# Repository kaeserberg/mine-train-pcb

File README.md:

# Le Train de la Mine - PCB

## Illustrations

<br/>

## Schéma

[Schéma électronique](train-de-mine-schematic.pdf)

## Commande de matériel

- [1 x 8p (1 x 12 pièces)](https://fr.aliexpress.com/item/1005005946834644.html)
- [3 x 2p (3 x 50 pièces)](https://fr.aliexpress.com/item/1005005946834644.html)
- [5x jeu de montage DRG-02](https://fr.aliexpress.com/item/32824633947.html)
- [5x rail DIN 30cm](https://fr.aliexpress.com/item/4001298414947.html)
- [5x ESP32-S3 Mini](https://fr.aliexpress.com/item/1005005449219195.html)
- [1x Connecteur femelle à 2x8 broches (50 pièces)](https://fr.aliexpress.com/item/32604411845.html)

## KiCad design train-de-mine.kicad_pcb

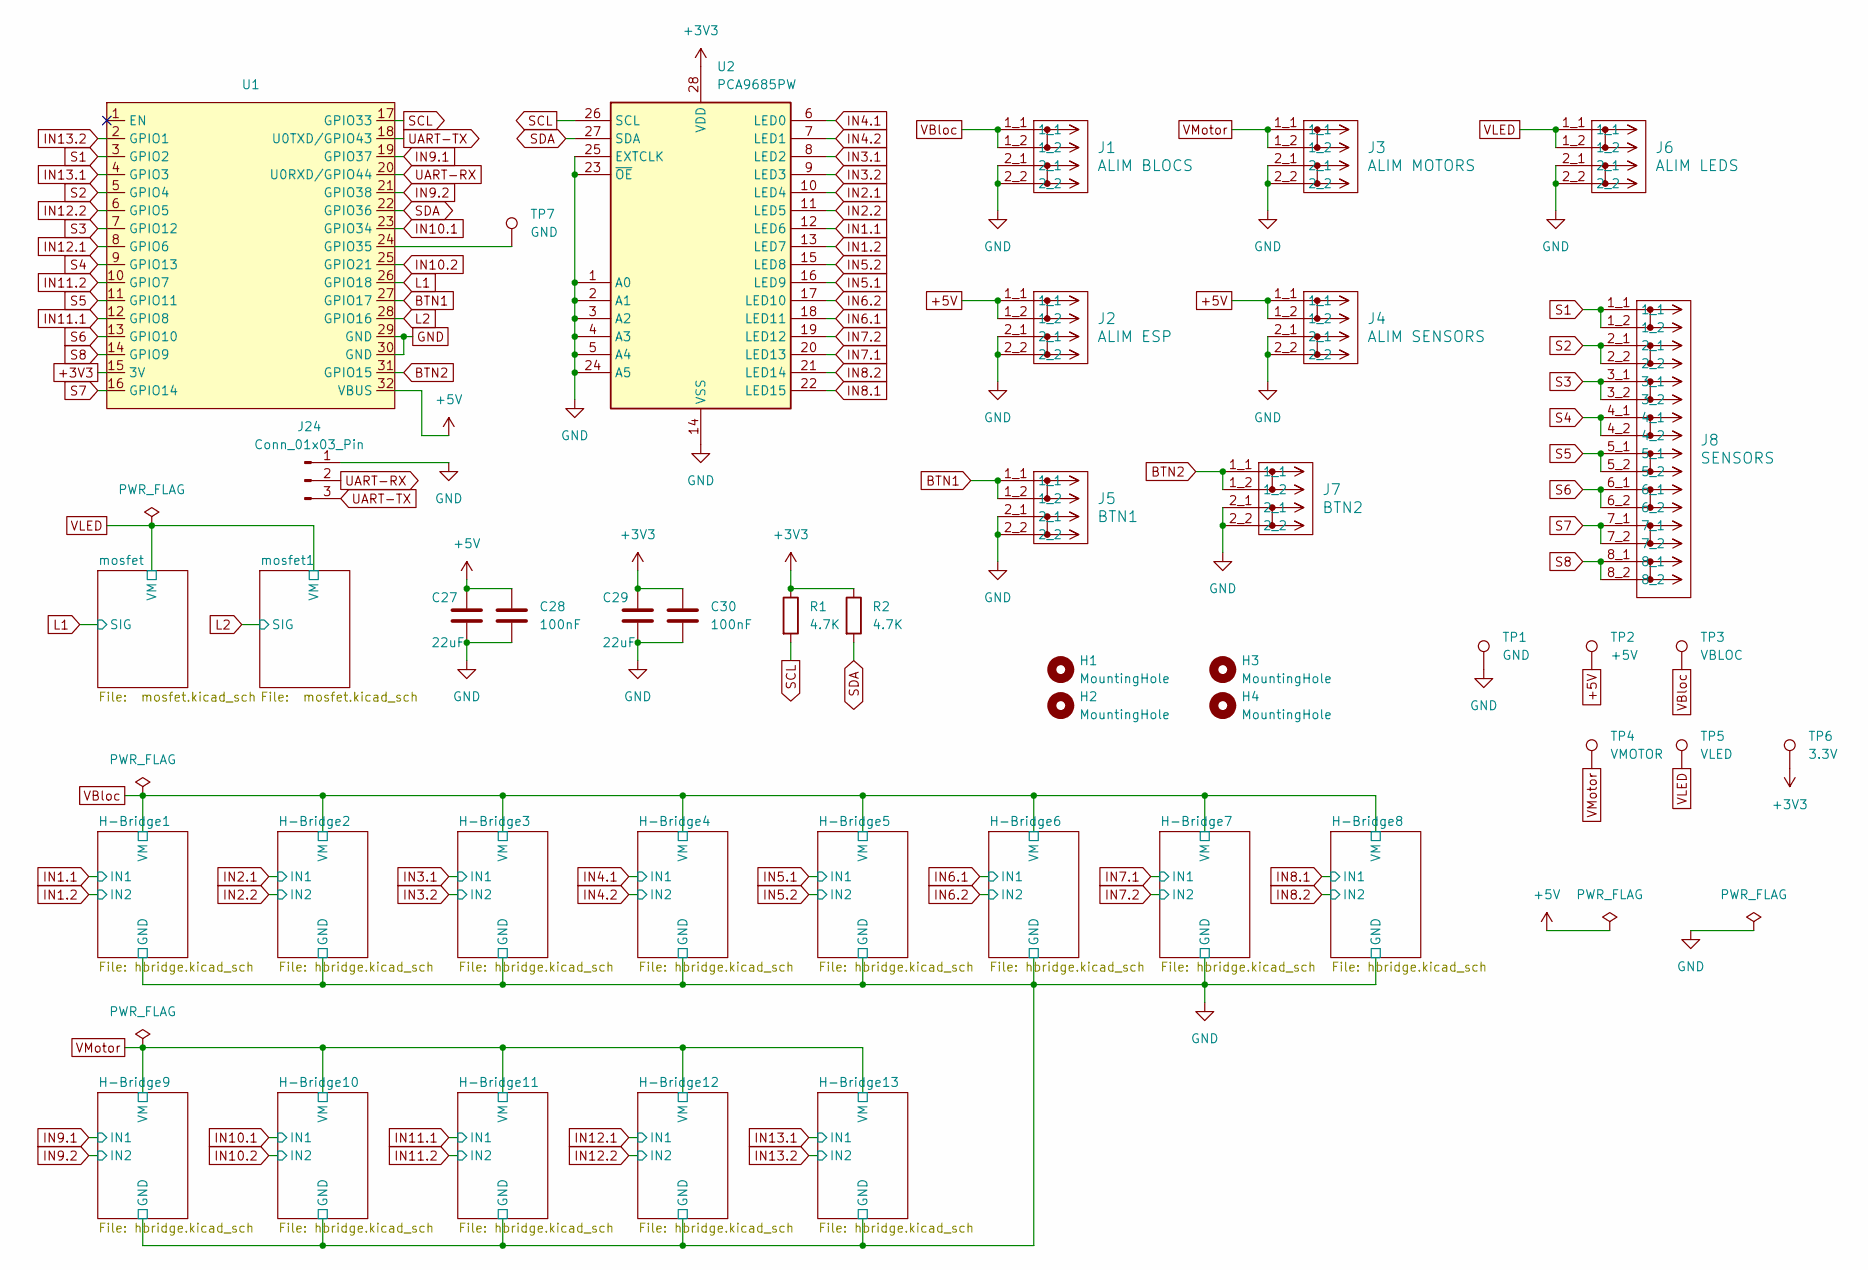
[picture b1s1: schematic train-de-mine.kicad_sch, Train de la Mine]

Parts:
C27, C29: 22uF; C_0603_1608Metric; LCSC C86295
C28, C30: 100nF; C_0603_1608Metric; LCSC C1591
H1, H2, H3, H4: MountingHole; MountingHole_3.2mm_M3_DIN965_Pad
J1: ALIM BLOCS; KFM736L-5.0-2P
J2: ALIM ESP; KFM736L-5.0-2P
J3: ALIM MOTORS; KFM736L-5.0-2P
J4: ALIM SENSORS; KFM736L-5.0-2P
J5: BTN1; KFM736L-5.0-2P
J6: ALIM LEDS; KFM736L-5.0-2P
J7: BTN2; KFM736L-5.0-2P
J8: SENSORS; KFM736L-5.0-8P
J24: Conn_01x03_Pin; PinHeader_1x03_P2.54mm_Vertical
R1, R2: 4.7K; R_0603_1608Metric; LCSC C23162
TP1, TP7: GND; TestPoint_THTPad_1.0x1.0mm_Drill0.5mm
TP2: +5V; TestPoint_THTPad_1.0x1.0mm_Drill0.5mm
TP3: VBLOC; TestPoint_THTPad_1.0x1.0mm_Drill0.5mm
TP4: VMOTOR; TestPoint_THTPad_1.0x1.0mm_Drill0.5mm
TP5: VLED; TestPoint_THTPad_1.0x1.0mm_Drill0.5mm
TP6: 3.3V; TestPoint_THTPad_1.0x1.0mm_Drill0.5mm
U1: 1; S3 Mini
U2: PCA9685PW; TSSOP-28_4.4x9.7mm_P0.65mm; LCSC C2678753

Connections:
+3V3: C29.1, C30.1, R1.1, R2.1, TP6.1, U1.15 (3V), U2.28 (VDD)
+5V: C27.1, C28.1, J2.1_1, J2.1_2, J4.1_1, J4.1_2, TP2.1, U1.32 (VBUS)
BTN1: J5.1_1, J5.1_2, U1.27 (GPIO17)
BTN2: J7.1_1, J7.1_2, U1.31 (GPIO15)
GND: C27.2, C28.2, C29.2, C30.2, J1.2_1, J1.2_2, J2.2_1, J2.2_2, J3.2_1, J3.2_2, J4.2_1, J4.2_2, J5.2_1, J5.2_2, J6.2_1, J6.2_2, J7.2_1, J7.2_2, J24.1, TP1.1, U1.29 (GND), U1.30 (GND), U2.1 (A0), U2.2 (A1), U2.3 (A2), U2.4 (A3), U2.5 (A4), U2.14 (VSS), U2.23 (~OE), U2.24 (A5), U2.25 (EXTCLK); also elsewhere on the board
IN1.1: U2.12 (LED6); also elsewhere on the board
IN1.2: U2.13 (LED7); also elsewhere on the board
IN2.1: U2.10 (LED4); also elsewhere on the board
IN2.2: U2.11 (LED5); also elsewhere on the board
IN3.1: U2.8 (LED2); also elsewhere on the board
IN3.2: U2.9 (LED3); also elsewhere on the board
IN4.1: U2.6 (LED0); also elsewhere on the board
IN4.2: U2.7 (LED1); also elsewhere on the board
IN5.1: U2.16 (LED9); also elsewhere on the board
IN5.2: U2.15 (LED8); also elsewhere on the board
IN6.1: U2.18 (LED11); also elsewhere on the board
IN6.2: U2.17 (LED10); also elsewhere on the board
IN7.1: U2.20 (LED13); also elsewhere on the board
IN7.2: U2.19 (LED12); also elsewhere on the board
IN8.1: U2.22 (LED15); also elsewhere on the board
IN8.2: U2.21 (LED14); also elsewhere on the board
IN9.1: U1.19 (GPIO37); also elsewhere on the board
IN9.2: U1.21 (GPIO38); also elsewhere on the board
IN10.1: U1.23 (GPIO34); also elsewhere on the board
IN10.2: U1.25 (GPIO21); also elsewhere on the board
IN11.1: U1.12 (GPIO8); also elsewhere on the board
IN11.2: U1.10 (GPIO7); also elsewhere on the board
IN12.1: U1.8 (GPIO6); also elsewhere on the board
IN12.2: U1.6 (GPIO5); also elsewhere on the board
IN13.1: U1.4 (GPIO3); also elsewhere on the board
IN13.2: U1.2 (GPIO1); also elsewhere on the board
unnamed: TP7.1, U1.24 (GPIO35)
S1: J8.1_1, J8.1_2, U1.3 (GPIO2)
S2: J8.2_1, J8.2_2, U1.5 (GPIO4)
S3: J8.3_1, J8.3_2, U1.7 (GPIO12)
S4: J8.4_1, J8.4_2, U1.9 (GPIO13)
S5: J8.5_1, J8.5_2, U1.11 (GPIO11)
S6: J8.6_1, J8.6_2, U1.13 (GPIO10)
S7: J8.7_1, J8.7_2, U1.16 (GPIO14)
S8: J8.8_1, J8.8_2, U1.14 (GPIO9)
SCL: R1.2, U1.17 (GPIO33), U2.26 (SCL)
SDA: R2.2, U1.22 (GPIO36), U2.27 (SDA)
UART-RX: J24.2, U1.20 (U0RXD/GPIO44)
UART-TX: J24.3, U1.18 (U0TXD/GPIO43)
VBloc: J1.1_1, J1.1_2, TP3.1; also elsewhere on the board
VLED: J6.1_1, J6.1_2, TP5.1; also elsewhere on the board
VMotor: J3.1_1, J3.1_2, TP4.1; also elsewhere on the board

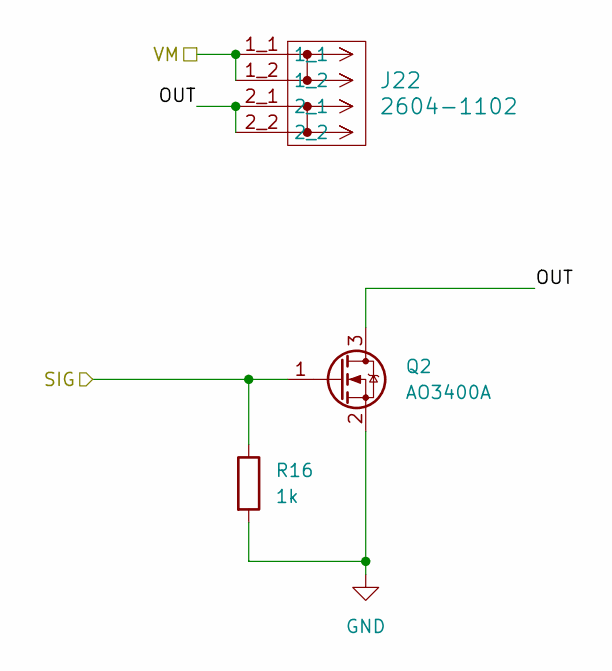
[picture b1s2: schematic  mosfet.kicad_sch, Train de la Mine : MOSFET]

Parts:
J22: 2604-1102; KFM736L-5.0-2P
Q2: AO3400A; SOT-23; LCSC C347475
R16: 1k; R_0603_1608Metric; LCSC C21190

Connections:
GND: Q2.2 (S), R16.2; also elsewhere on the board
VLED: J22.1_1, J22.1_2; also elsewhere on the board

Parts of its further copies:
J23: 2604-1102; KFM736L-5.0-2P
Q1: AO3400A; SOT-23; LCSC C347475
R17: 1k; R_0603_1608Metric; LCSC C21190

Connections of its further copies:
GND: Q1.2 (S), R17.2; also elsewhere on the board
VLED: J23.1_1, J23.1_2; also elsewhere on the board

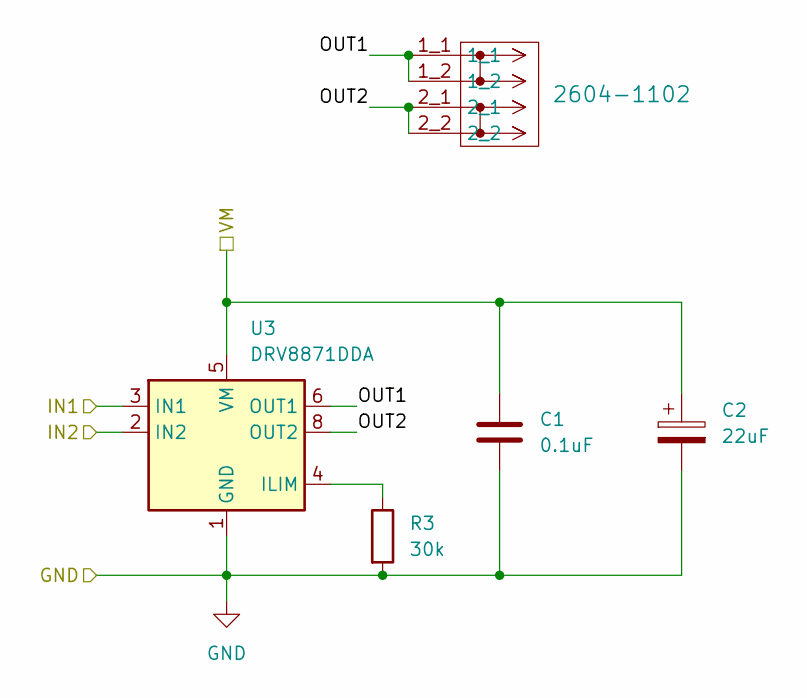
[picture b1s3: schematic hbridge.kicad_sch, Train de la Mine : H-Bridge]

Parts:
C1: 0.1uF; C_0805_2012Metric; LCSC C49678
C2: 22uF; CP_Elec_6.3x7.7; LCSC C242074
J9: 2604-1102; KFM736L-5.0-2P
R3: 30k; R_0603_1608Metric; LCSC C22984
U3: DRV8871DDA; Texas_HTSOP-8-1EP_3.9x4.9mm_P1.27mm_EP2.95x4.9mm_Mask2.4x3.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; LCSC C75864

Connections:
/H-Bridge1/OUT1: J9.1_1, J9.1_2, U3.6 (OUT1)
/H-Bridge1/OUT2: J9.2_1, J9.2_2, U3.8 (OUT2)
GND: C1.2, C2.2, R3.2, U3.1 (GND), U3.7 (GND), U3.9 (GND); also elsewhere on the board
IN1.1: U3.3 (IN1); also elsewhere on the board
IN1.2: U3.2 (IN2); also elsewhere on the board
unnamed: R3.1, U3.4 (ILIM)
VBloc: C1.1, C2.1, U3.5 (VM); also elsewhere on the board

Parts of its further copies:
C3, C5, C7, C9, C11, C13, C15, C17, C19, C21, C23, C25: 0.1uF; C_0805_2012Metric; LCSC C49678
C4, C6, C8, C10, C12, C14, C16, C18, C20, C22, C24, C26: 22uF; CP_Elec_6.3x7.7; LCSC C242074
J10, J11, J12, J13, J14, J15, J16, J17, J18, J19, J20, J21: 2604-1102; KFM736L-5.0-2P
R4, R5, R6, R7, R8, R9, R10, R11, R12, R13, R14, R15: 30k; R_0603_1608Metric; LCSC C22984
U4, U5, U6, U7, U8, U9, U10, U11, U12, U13, U14, U15: DRV8871DDA; Texas_HTSOP-8-1EP_3.9x4.9mm_P1.27mm_EP2.95x4.9mm_Mask2.4x3.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; LCSC C75864

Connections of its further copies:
/H-Bridge2/OUT1: J10.1_1, J10.1_2, U4.6 (OUT1)
/H-Bridge2/OUT2: J10.2_1, J10.2_2, U4.8 (OUT2)
/H-Bridge3/OUT1: J11.1_1, J11.1_2, U5.6 (OUT1)
/H-Bridge3/OUT2: J11.2_1, J11.2_2, U5.8 (OUT2)
/H-Bridge4/OUT1: J12.1_1, J12.1_2, U6.6 (OUT1)
/H-Bridge4/OUT2: J12.2_1, J12.2_2, U6.8 (OUT2)
/H-Bridge5/OUT1: J13.1_1, J13.1_2, U7.6 (OUT1)
/H-Bridge5/OUT2: J13.2_1, J13.2_2, U7.8 (OUT2)
/H-Bridge6/OUT1: J14.1_1, J14.1_2, U8.6 (OUT1)
/H-Bridge6/OUT2: J14.2_1, J14.2_2, U8.8 (OUT2)
/H-Bridge7/OUT1: J15.1_1, J15.1_2, U9.6 (OUT1)
/H-Bridge7/OUT2: J15.2_1, J15.2_2, U9.8 (OUT2)
/H-Bridge8/OUT1: J16.1_1, J16.1_2, U10.6 (OUT1)
/H-Bridge8/OUT2: J16.2_1, J16.2_2, U10.8 (OUT2)
/H-Bridge9/OUT1: J17.1_1, J17.1_2, U11.6 (OUT1)
/H-Bridge9/OUT2: J17.2_1, J17.2_2, U11.8 (OUT2)
/H-Bridge10/OUT1: J18.1_1, J18.1_2, U12.6 (OUT1)
/H-Bridge10/OUT2: J18.2_1, J18.2_2, U12.8 (OUT2)
/H-Bridge11/OUT1: J19.1_1, J19.1_2, U13.6 (OUT1)
/H-Bridge11/OUT2: J19.2_1, J19.2_2, U13.8 (OUT2)
/H-Bridge12/OUT1: J20.1_1, J20.1_2, U14.6 (OUT1)
/H-Bridge12/OUT2: J20.2_1, J20.2_2, U14.8 (OUT2)
/H-Bridge13/OUT1: J21.1_1, J21.1_2, U15.6 (OUT1)
/H-Bridge13/OUT2: J21.2_1, J21.2_2, U15.8 (OUT2)
GND: C3.2, C4.2, C5.2, C6.2, C7.2, C8.2, C9.2, C10.2, C11.2, C12.2, C13.2, C14.2, C15.2, C16.2, C17.2, C18.2, C19.2, C20.2, C21.2, C22.2, C23.2, C24.2, C25.2, C26.2, R4.2, R5.2, R6.2, R7.2, R8.2, R9.2, R10.2, R11.2, R12.2, R13.2, R14.2, R15.2, U4.1 (GND), U4.7 (GND), U4.9 (GND), U5.1 (GND), U5.7 (GND), U5.9 (GND), U6.1 (GND), U6.7 (GND), U6.9 (GND), U7.1 (GND), U7.7 (GND), U7.9 (GND), U8.1 (GND), U8.7 (GND), U8.9 (GND), U9.1 (GND), U9.7 (GND), U9.9 (GND), U10.1 (GND), U10.7 (GND), U10.9 (GND), U11.1 (GND), U11.7 (GND), U11.9 (GND), U12.1 (GND), U12.7 (GND), U12.9 (GND), U13.1 (GND), U13.7 (GND), U13.9 (GND), U14.1 (GND), U14.7 (GND), U14.9 (GND), U15.1 (GND), U15.7 (GND), U15.9 (GND); also elsewhere on the board
IN2.1: U4.3 (IN1); also elsewhere on the board
IN2.2: U4.2 (IN2); also elsewhere on the board
IN3.1: U5.3 (IN1); also elsewhere on the board
IN3.2: U5.2 (IN2); also elsewhere on the board
IN4.1: U6.3 (IN1); also elsewhere on the board
IN4.2: U6.2 (IN2); also elsewhere on the board
IN5.1: U7.3 (IN1); also elsewhere on the board
IN5.2: U7.2 (IN2); also elsewhere on the board
IN6.1: U8.3 (IN1); also elsewhere on the board
IN6.2: U8.2 (IN2); also elsewhere on the board
IN7.1: U9.3 (IN1); also elsewhere on the board
IN7.2: U9.2 (IN2); also elsewhere on the board
IN8.1: U10.3 (IN1); also elsewhere on the board
IN8.2: U10.2 (IN2); also elsewhere on the board
IN9.1: U11.3 (IN1); also elsewhere on the board
IN9.2: U11.2 (IN2); also elsewhere on the board
IN10.1: U12.3 (IN1); also elsewhere on the board
IN10.2: U12.2 (IN2); also elsewhere on the board
IN11.1: U13.3 (IN1); also elsewhere on the board
IN11.2: U13.2 (IN2); also elsewhere on the board
IN12.1: U14.3 (IN1); also elsewhere on the board
IN12.2: U14.2 (IN2); also elsewhere on the board
IN13.1: U15.3 (IN1); also elsewhere on the board
IN13.2: U15.2 (IN2); also elsewhere on the board
unnamed: R4.1, U4.4 (ILIM)
unnamed: R5.1, U5.4 (ILIM)
unnamed: R6.1, U6.4 (ILIM)
unnamed: R7.1, U7.4 (ILIM)
unnamed: R8.1, U8.4 (ILIM)
unnamed: R9.1, U9.4 (ILIM)
unnamed: R10.1, U10.4 (ILIM)
unnamed: R11.1, U11.4 (ILIM)
unnamed: R12.1, U12.4 (ILIM)
unnamed: R13.1, U13.4 (ILIM)
unnamed: R14.1, U14.4 (ILIM)
unnamed: R15.1, U15.4 (ILIM)
VBloc: C3.1, C4.1, C5.1, C6.1, C7.1, C8.1, C9.1, C10.1, C11.1, C12.1, C13.1, C14.1, C15.1, C16.1, U4.5 (VM), U5.5 (VM), U6.5 (VM), U7.5 (VM), U8.5 (VM), U9.5 (VM), U10.5 (VM); also elsewhere on the board
VMotor: C17.1, C18.1, C19.1, C20.1, C21.1, C22.1, C23.1, C24.1, C25.1, C26.1, U11.5 (VM), U12.5 (VM), U13.5 (VM), U14.5 (VM), U15.5 (VM); also elsewhere on the board

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
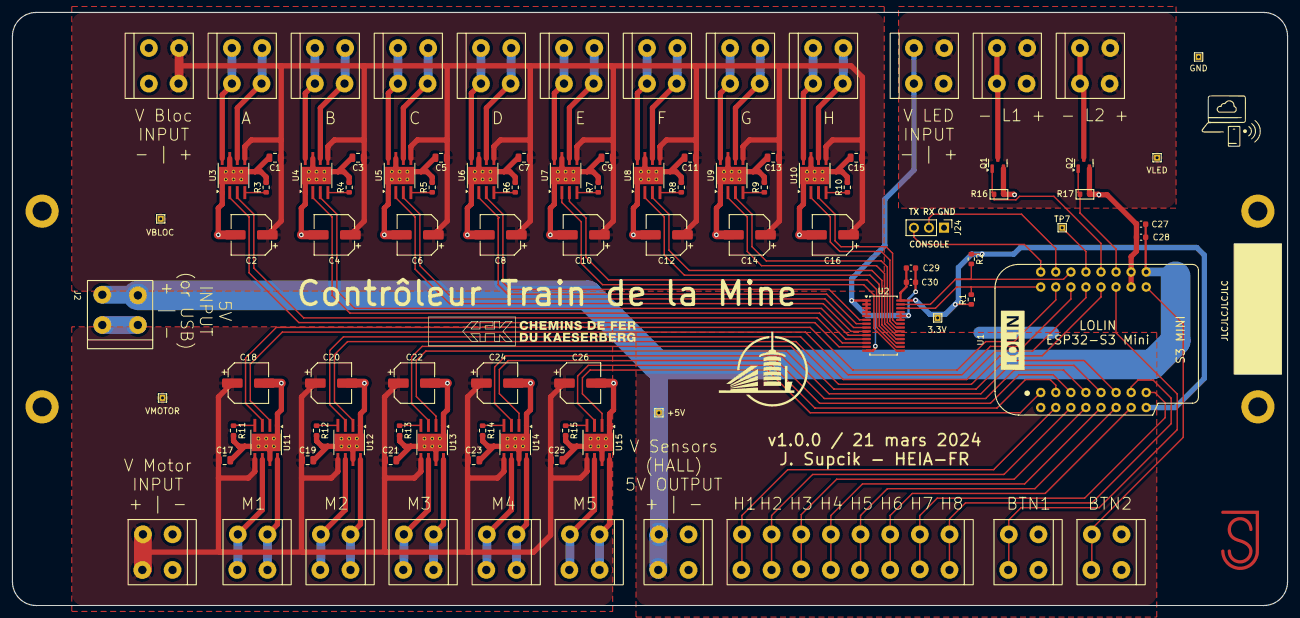
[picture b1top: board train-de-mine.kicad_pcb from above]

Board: 2 copper layers, 215.0 x 100.0 mm, 100 parts (0 on the bottom side), 90 nets.

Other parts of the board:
CFK Logo: LOGO
